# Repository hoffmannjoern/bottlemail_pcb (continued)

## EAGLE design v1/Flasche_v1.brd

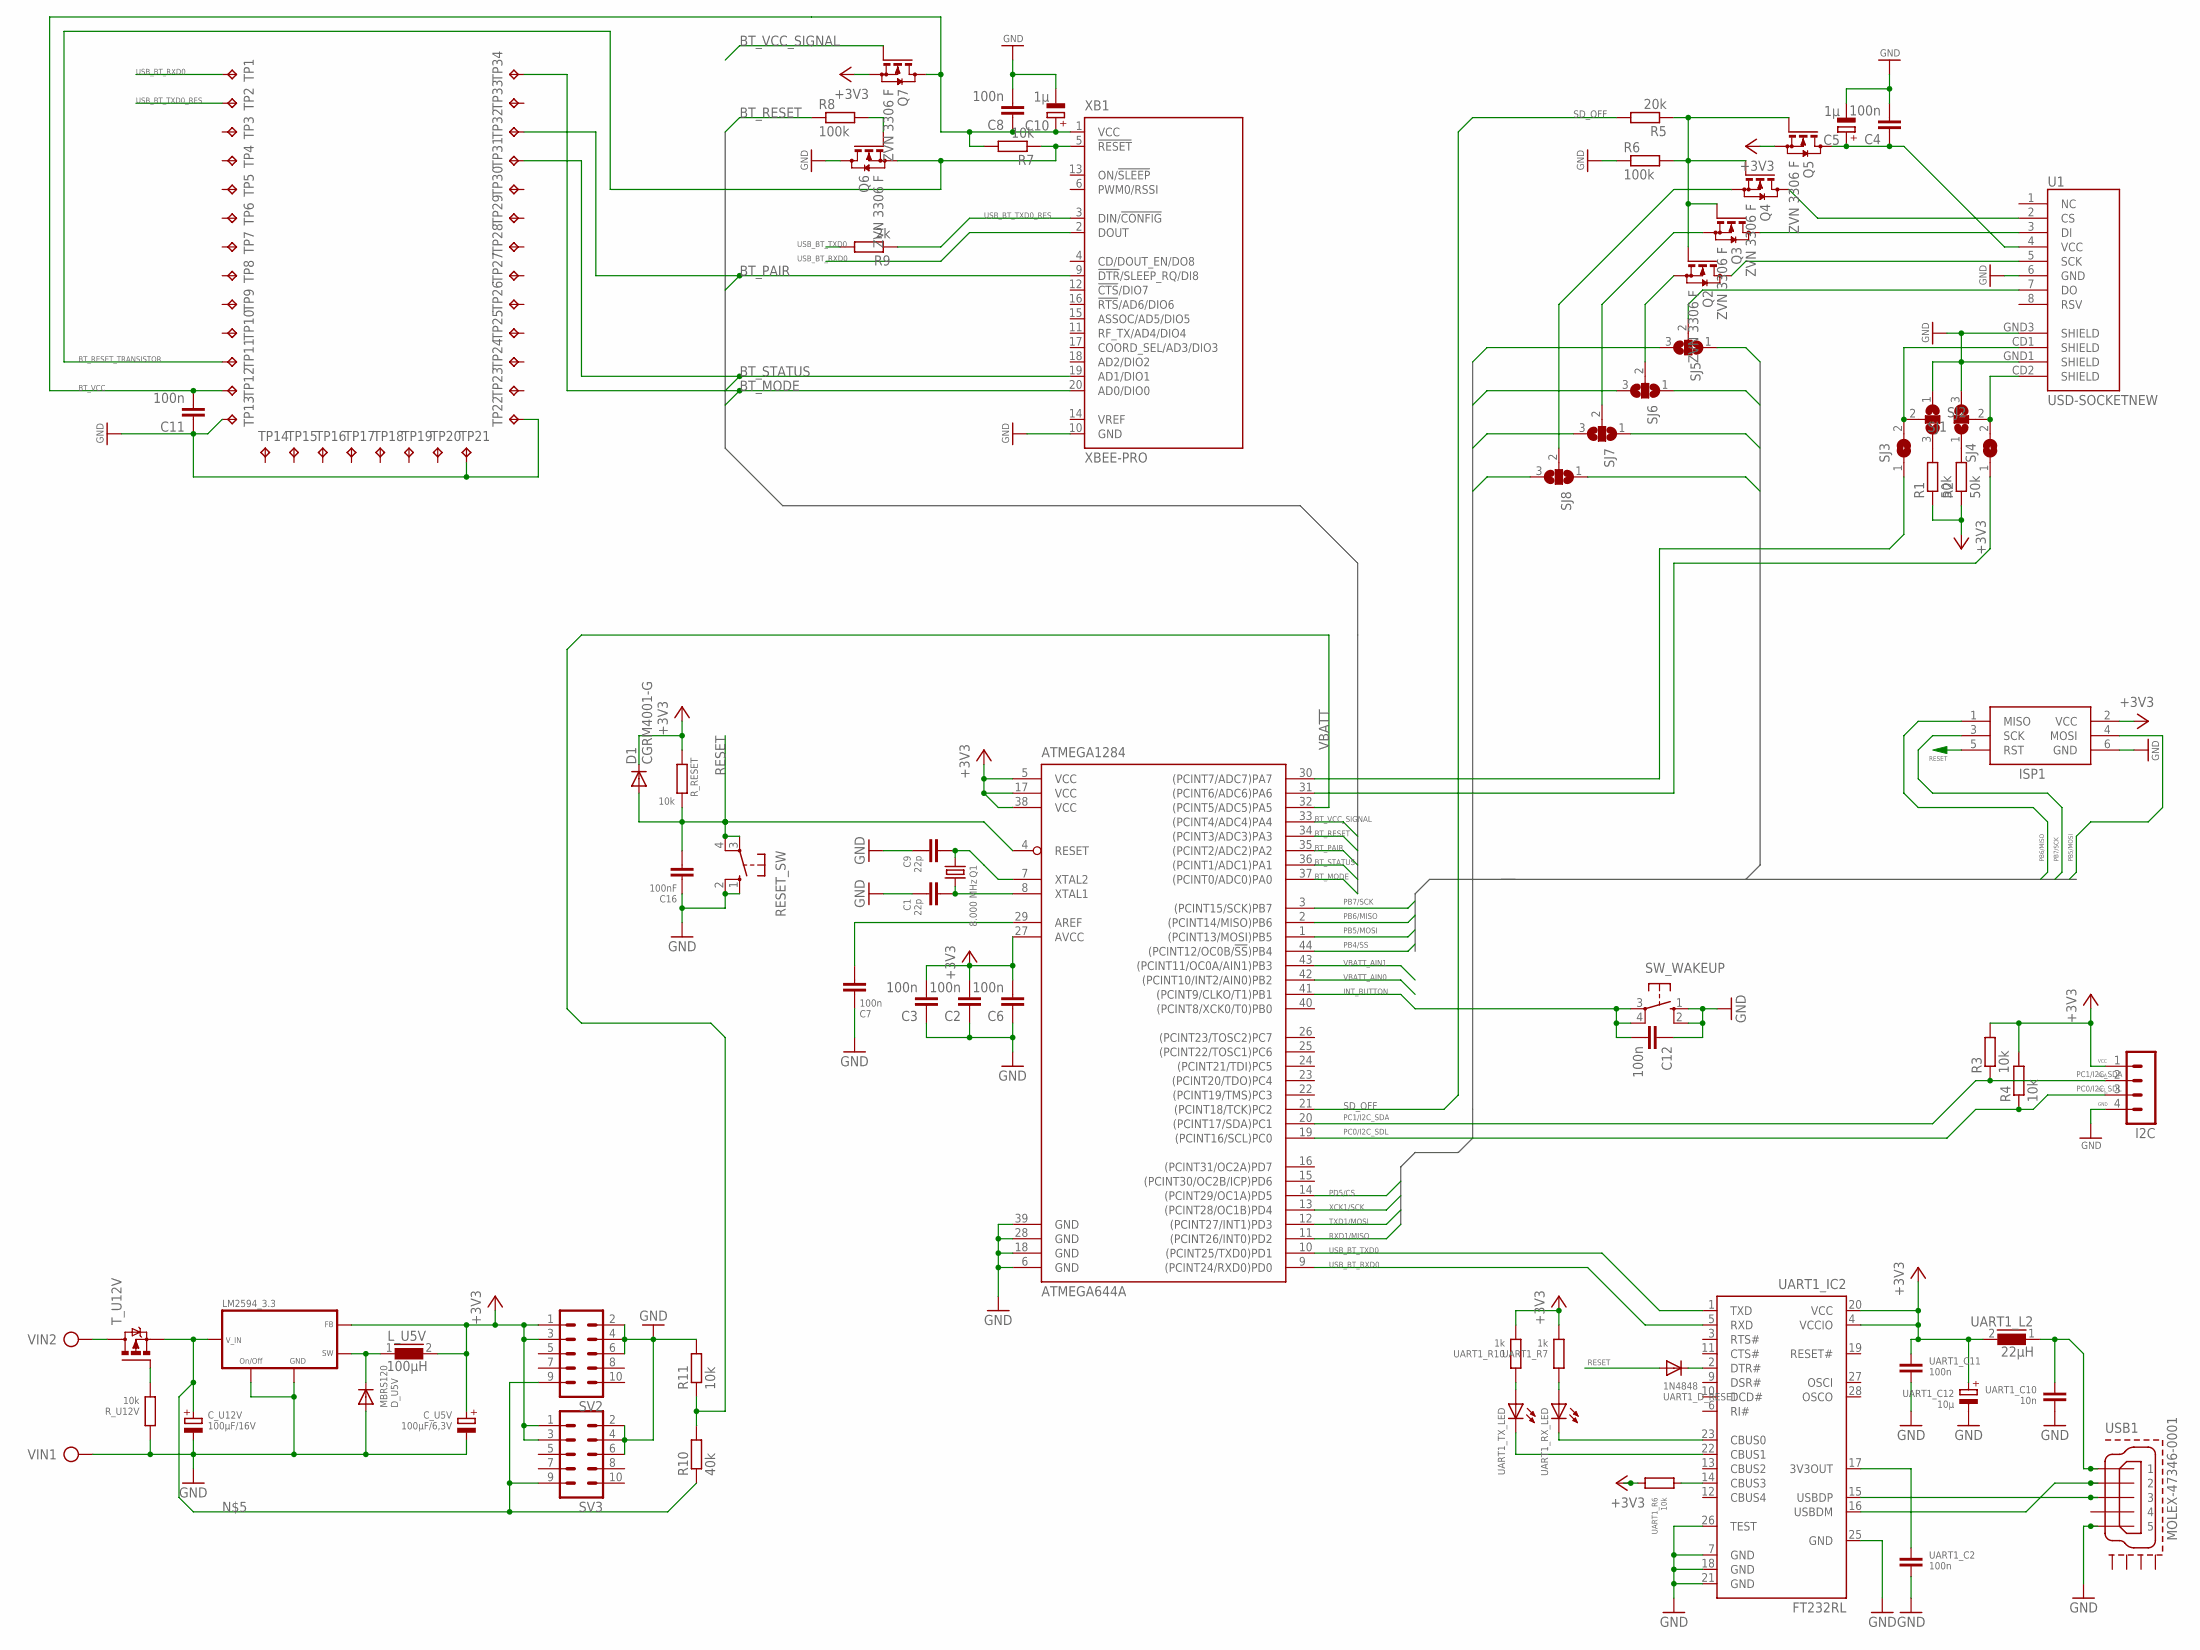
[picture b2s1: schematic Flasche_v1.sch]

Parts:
ATMEGA1284: ATMEGA644A; TQFP44
C1, C9: 22p; C0805
C2, C3, C4, C6, C7, C8, C11, C12: 100n; C0805
C5, C10: 1µ; SMC_D
C16: 100nF; C0805
C_U5V: 100µF/6,3V; SMC_D
C_U12V: 100µF/16V; SMC_D
D1: CGRM4001-G; SOD-123_MINI-SMA
D_U5V: MBRS120; SMB
I2C: MA04-1
ISP1: AVRISP-6; AVRISP
LM2594_3.3: LM2594; SO08
L_U5V: 100µH; PISM
Q1: 8.000 MHz; HC18U-V
Q2, Q3, Q4, Q5, Q6, Q7: ZVN 3306 F; SOT23
R1, R2: 50k; M1206
R3, R4, R7, R11: 10k; M1206
R5: 20k; M1206
R6, R8: 100k; M1206
R9: 2k; M1206
R10: 40k; M1206
RESET_SW: 10-XX; B3F-10XX
R_RESET: 10k; R0805
R_U12V: 10k; R0805
SJ1, SJ2, SJ5, SJ6, SJ7, SJ8: SJ2W; SJ_2
SJ3, SJ4: SJ
SV2, SV3: ML10L
SW_WAKEUP: 10-XX; B3F-10XX
TP1, TP2, TP3, TP4, TP5, TP6, TP7, TP8, TP9, TP10, TP11, TP12, TP13, TP14, TP15, TP16, TP17, TP18, TP19, TP20, TP21, TP22, TP23, TP24, TP25, TP26, TP27, TP28, TP29, TP30, TP31, TP32, TP33, TP34: TPTP06SQ; TP06SQ
T_U12V: MOS_P_SOT23_GDS; SOT23
U1: USD-SOCKETNEW; MICRO-SD-SOCKET-PP
UART1_C2, UART1_C11: 100n; C0805
UART1_C10: 10n; C0805
UART1_C12: 10µ; SMC_D
UART1_D_RESET: 1N4848; MINIMELF
UART1_IC2: FT232RL; SSOP28
UART1_L2: 22µH; PIS2408
UART1_R6: 10k; R0805
UART1_R7, UART1_R10: 1k; R0805
UART1_RX_LED, UART1_TX_LED: LEDCHIPLED_0805; CHIPLED_0805
USB1: MOLEX-47346-0001; MOLEX-47364-0001
VIN: AK350/2
XB1: XBEE-PRO

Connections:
+3V3: ATMEGA1284.5 (VCC), ATMEGA1284.17 (VCC), ATMEGA1284.27 (AVCC), ATMEGA1284.38 (VCC), C2.2, C3.2, C6.2, C_U5V.+, D1.C, I2C.1, ISP1.2 (VCC), LM2594_3.3.4 (FB), L_U5V.2, Q5.2 (S), Q7.2 (S), R1.1, R2.1, R3.2, R4.2, R_RESET.2, SV2.1, SV2.3, SV3.1, SV3.3, UART1_C11.1, UART1_C12.+, UART1_IC2.4 (VCCIO), UART1_IC2.20 (VCC), UART1_L2.2, UART1_R6.2, UART1_R7.1, UART1_R10.1
AREF: ATMEGA1284.29 (AREF), C7.2
BT_MODE: ATMEGA1284.37 ((PCINT0/ADC0)PA0), TP34.TP, XB1.20 (AD0/DIO0)
BT_PAIR: ATMEGA1284.35 ((PCINT2/ADC2)PA2), TP32.TP, XB1.9 (!DTR!/SLEEP_RQ/DI8)
BT_RESET: ATMEGA1284.34 ((PCINT3/ADC3)PA3), R8.1
BT_RESET_TRANSISTOR: Q6.2 (S), R7.1, TP11.TP, XB1.5 (!RESET)
BT_STATUS: ATMEGA1284.36 ((PCINT1/ADC1)PA1), TP31.TP, XB1.19 (AD1/DIO1)
BT_VCC: C8.1, C10.+, C11.2, Q7.3 (D), R7.2, TP12.TP, XB1.1 (VCC)
BT_VCC_SIGNAL: ATMEGA1284.33 ((PCINT4/ADC4)PA4), Q7.1 (G)
DTR#: UART1_D_RESET.C, UART1_IC2.2 (DTR#)
GND: ATMEGA1284.6 (GND), ATMEGA1284.18 (GND), ATMEGA1284.28 (GND), ATMEGA1284.39 (GND), C1.1, C2.1, C3.1, C4.2, C5.-, C6.1, C7.1, C8.2, C9.1, C10.-, C11.1, C12.1, C16.1, C_U5V.-, C_U12V.-, D_U5V.A, I2C.4, ISP1.6 (GND), LM2594_3.3.5 (ON/OFF), LM2594_3.3.6 (GND), Q6.3 (D), R6.1, R11.2, RESET_SW.1 (S), RESET_SW.2 (S1), R_U12V.2, SJ1.3, SJ2.1, SV2.2, SV2.4, SV2.6, SV3.2, SV3.4, SV3.6, SW_WAKEUP.1 (S), SW_WAKEUP.2 (S1), TP13.TP, TP21.TP, TP22.TP, U1.6 (GND), U1.GND1 (SHIELD), U1.GND3 (SHIELD), UART1_C2.2, UART1_C10.2, UART1_C11.2, UART1_C12.-, UART1_IC2.7 (GND), UART1_IC2.18 (GND), UART1_IC2.21 (GND), UART1_IC2.25 (GND), UART1_IC2.26 (TEST), USB1.5, VIN.P$1, XB1.10 (GND)
INT_BUTTON: ATMEGA1284.41 ((PCINT9/CLKO/T1)PB1), C12.2, SW_WAKEUP.3, SW_WAKEUP.4 (P1)
unnamed: UART1_R10.2, UART1_TX_LED.A
unnamed: UART1_C2.1, UART1_IC2.17 (3V3OUT)
unnamed: T_U12V.2 (D), VIN.P$2
unnamed: UART1_IC2.16 (USBDM), USB1.2
unnamed: C_U12V.+, LM2594_3.3.7 (IN), R10.1, SV2.9, SV3.9, T_U12V.3 (S)
unnamed: UART1_R7.2, UART1_RX_LED.A
unnamed: UART1_IC2.15 (USBDP), USB1.3
unnamed: UART1_IC2.14 (CBUS3), UART1_R6.1
unnamed: UART1_C10.1, UART1_L2.1, USB1.1
unnamed: UART1_IC2.23 (CBUS0), UART1_RX_LED.C
unnamed: UART1_IC2.22 (CBUS1), UART1_TX_LED.C
unnamed: SJ2.2, SJ3.2, U1.CD1 (SHIELD)
unnamed: SJ1.2, SJ4.2, U1.CD2 (SHIELD)
unnamed: R_U12V.1, T_U12V.1 (G)
unnamed: ATMEGA1284.31 ((PCINT6/ADC6)PA6), SJ4.1
unnamed: R1.2, SJ2.3
unnamed: R2.2, SJ1.1
unnamed: SJ5.2, U1.7 (DO)
unnamed: ATMEGA1284.30 ((PCINT7/ADC7)PA7), SJ3.1
unnamed: Q2.2 (S), SJ6.2
unnamed: Q3.2 (S), SJ7.2
unnamed: Q4.3 (D), U1.2 (CS)
unnamed: Q3.3 (D), U1.3 (DI)
unnamed: Q2.3 (D), U1.5 (SCK)
unnamed: C4.1, C5.+, Q5.3 (D), U1.4 (VCC)
unnamed: Q2.1 (G), Q3.1 (G), Q4.1 (G), Q5.1 (G), R5.1, R6.2
unnamed: Q6.1 (G), R8.2
PB4/SS: ATMEGA1284.44 ((PCINT12/OC0B/!SS!)PB4), SJ8.1
PB5/MOSI: ATMEGA1284.1 ((PCINT13/MOSI)PB5), ISP1.4 (MOSI), SJ7.1
PB6/MISO: ATMEGA1284.2 ((PCINT14/MISO)PB6), ISP1.1 (MISO), SJ5.1
PB7/SCK: ATMEGA1284.3 ((PCINT15/SCK)PB7), ISP1.3 (SCK), SJ6.1
PC0/I2C_SDL: ATMEGA1284.19 ((PCINT16/SCL)PC0), I2C.3, R4.1
PC1/I2C_SDA: ATMEGA1284.20 ((PCINT17/SDA)PC1), I2C.2, R3.1
PD5/CS: ATMEGA1284.14 ((PCINT29/OC1A)PD5), SJ8.3
RESET: ATMEGA1284.4 (RESET), C16.2, D1.A, ISP1.5 (RST), RESET_SW.3, RESET_SW.4 (P1), R_RESET.1, UART1_D_RESET.A
RXD1/MISO: ATMEGA1284.11 ((PCINT26/INT0)PD2), SJ5.3
SD_CS: Q4.2 (S), SJ8.2
SD_OFF: ATMEGA1284.21 ((PCINT18/TCK)PC2), R5.2
SWITCH_OUT: D_U5V.C, LM2594_3.3.8 (SW), L_U5V.1
TXD1/MOSI: ATMEGA1284.12 ((PCINT27/INT1)PD3), SJ7.3
USB_BT_RXD0: ATMEGA1284.9 ((PCINT24/RXD0)PD0), TP1.TP, UART1_IC2.5 (RXD), XB1.2 (DOUT)
USB_BT_TXD0: ATMEGA1284.10 ((PCINT25/TXD0)PD1), R9.2, UART1_IC2.1 (TXD)
USB_BT_TXD0_RES: R9.1, TP2.TP, XB1.3 (DIN/!CONFIG)
VBATT: ATMEGA1284.32 ((PCINT5/ADC5)PA5), R10.2, R11.1
VBATT_AIN0: ATMEGA1284.42 ((PCINT10/INT2/AIN0)PB2)
VBATT_AIN1: ATMEGA1284.43 ((PCINT11/OC0A/AIN1)PB3)
XCK1/SCK: ATMEGA1284.13 ((PCINT28/OC1B)PD4), SJ6.3
XTAL1: ATMEGA1284.8 (XTAL1), C1.2, Q1.1
XTAL2: ATMEGA1284.7 (XTAL2), C9.2, Q1.2

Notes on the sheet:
VCC
SDA
SCL
GND

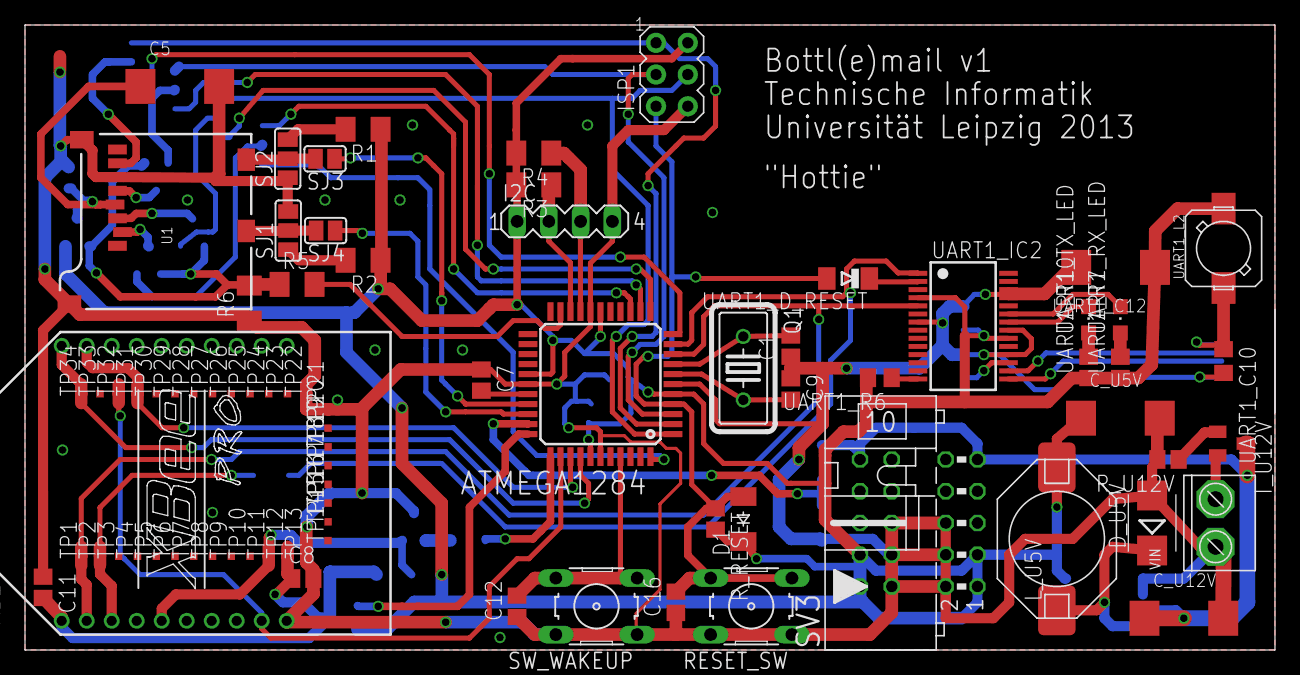
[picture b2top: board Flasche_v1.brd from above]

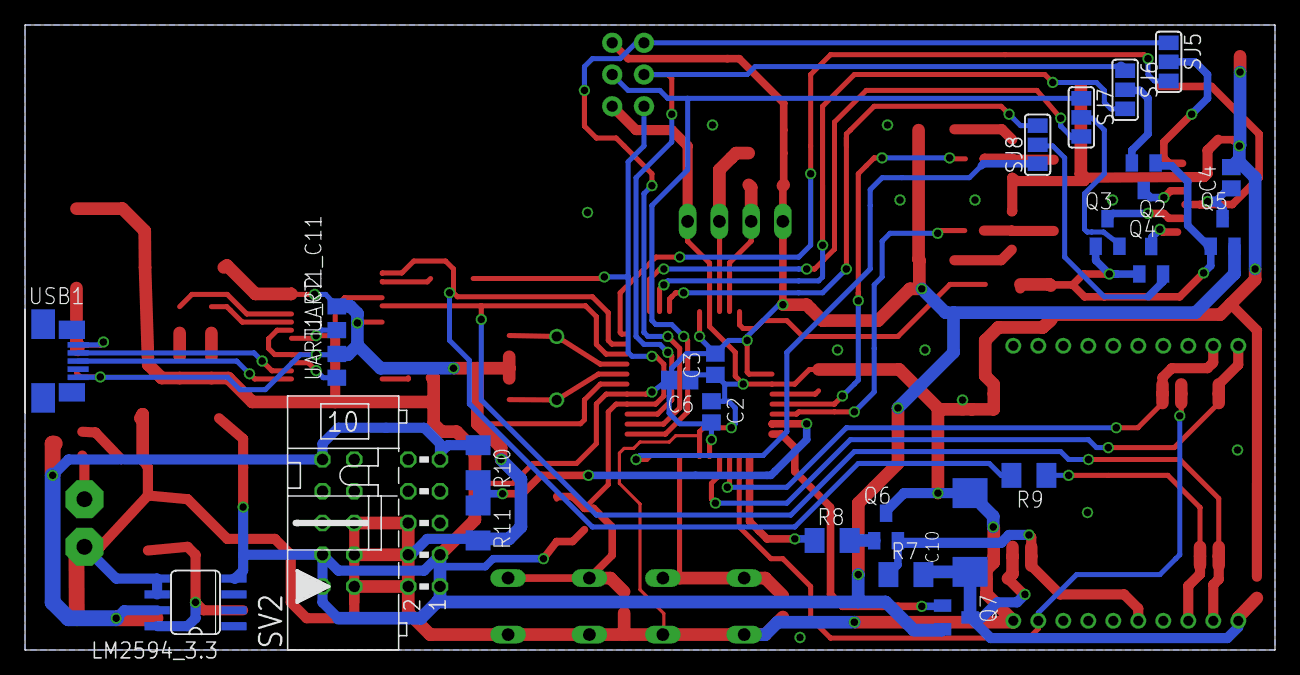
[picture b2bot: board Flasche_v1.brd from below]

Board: 2 copper layers, 100.0 x 50.0 mm, 105 parts (25 on the bottom side), 59 nets.

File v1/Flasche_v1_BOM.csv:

Qty;Value;Device;Package;Parts;Description;MF;MPN;OC_FARNELL;OC_NEWARK;TP_SIGNAL_NAME
2;;10-XX;B3F-10XX;RESET_SW, SW_WAKEUP;OMRON SWITCH;;B3F-1000;176432;36M3542;
2;;LEDCHIPLED_0805;CHIPLED_0805;UART1_RX_LED, UART1_TX_LED;LED;;;;;
1;;MA04-1;MA04-1;I2C;PIN HEADER;;;unknown;unknown;
2;;ML10L;ML10L;SV2, SV3;HARTING;;;unknown;unknown;
1;;MOS_P_SOT23_GDS;SOT23;T_U12V;P - CHANNEL ENHANCEMENT MODE (POWER ) MOS TRANSISTOR;;;;;
2;;SJ;SJ;SJ3, SJ4;SMD solder JUMPER;;;;;
6;;SJ2W;SJ_2;SJ1, SJ2, SJ5, SJ6, SJ7, SJ8;SMD solder JUMPER;;;;;
2;100k;R-EU_M1206;M1206;R6, R8;RESISTOR, European symbol;;;;;
8;100n;C-0805;C0805;C2, C3, C4, C6, C7, C8, C11, C12;Capacitor;;;;;
2;100n;C-EUC0805;C0805;UART1_C2, UART1_C11;CAPACITOR, European symbol;;;;;
1;100nF;C-0805;C0805;C16;Capacitor;;;;;
1;100µF/16V;CPOL-EUSMCD;SMC_D;C_U12V;POLARIZED CAPACITOR, European symbol;;;;;
1;100µF/6,3V;CPOL-EUSMCD;SMC_D;C_U5V;POLARIZED CAPACITOR, European symbol;;;;;
1;100µH;L_PISM;PISM;L_U5V;INDUCTOR;;;;;
4;10k;R-EU_M1206;M1206;R3, R4, R7, R11;RESISTOR, European symbol;;;;;
1;10k;R-EU_R0805;R0805;UART1_R6;RESISTOR, European symbol;;;;;
2;10k;R-R0805;R0805;R_RESET, R_U12V;Resistor;;;;;
1;10n;C-EUC0805;C0805;UART1_C10;CAPACITOR, European symbol;;;;;
1;10µ;CPOL-EUSMCD;SMC_D;UART1_C12;POLARIZED CAPACITOR, European symbol;;;;;
1;1N4848;D_MINIMELF;MINIMELF;UART1_D_RESET;DIODE;;;;;
2;1k;R-R0805;R0805;UART1_R7, UART1_R10;Resistor;;;;;
2;1µ;CPOL-EUSMCD;SMC_D;C5, C10;POLARIZED CAPACITOR, European symbol;;;;;
1;20k;R-EU_M1206;M1206;R5;RESISTOR, European symbol;;;;;
2;22p;C-0805;C0805;C1, C9;Capacitor;;;;;
1;22µH;L_PIS2408;PIS2408;UART1_L2;INDUCTOR;;;;;
1;2k;R-EU_M1206;M1206;R9;RESISTOR, European symbol;;;;;
1;40k;R-EU_M1206;M1206;R10;RESISTOR, European symbol;;;;;
2;50k;R-EU_M1206;M1206;R1, R2;RESISTOR, European symbol;;;;;
1;8.000 MHz;CRYSTALHC18U-V;HC18U-V;Q1;CRYSTAL;;;unknown;unknown;
1;AK350/2;AK350/2;AK350/2;VIN;CONNECTOR Raster: 3,5mm;;;;;
1;ATMEGA644A;ATMEGA644A;TQFP44;ATMEGA1284;8-bit Microcontroller with 64K Bytes In-System Programmable Flash;;ATMEGA644PV-10AU;1455123;58M3748;
1;AVRISP-6;AVRISP-6;AVRISP;ISP1;AVR ISP HEADER;;;;;
1;CGRM4001-G;CGRM4001-G;SOD-123_MINI-SMA;D1;Molded plasitc,JEDEC SOD-123/Mini SMA;;;;;
1;FT232RL;FT232RL;SSOP28;UART1_IC2;Source: http://www.ftdichip.com/Documents/DataSheets/DS_FT232R_v104.pdf;;;;;
1;LM2594;LM2594;SO08;LM2594_3.3;LM2594/LM2594HV;;;;;
1;MBRS120;D_SMB;SMB;D_U5V;DIODE;;;;;
1;MOLEX-47346-0001;MOLEX-47346-0001;MOLEX-47364-0001;USB1;MICRO USB B, BOTTOM MOUNT;;;;;
34;TPTP06SQ;TPTP06SQ;TP06SQ;TP1, TP2, TP3, TP4, TP5, TP6, TP7, TP8, TP9, TP10, TP11, TP12, TP13, TP14, TP15, TP16, TP17, TP18, TP19, TP20, TP21, TP22, TP23, TP24, TP25, TP26, TP27, TP28, TP29, TP30, TP31, TP32, TP33, TP34;Test pad;;;;;
1;USD-SOCKETNEW;USD-SOCKETNEW;MICRO-SD-SOCKET-PP;U1;microSD Socket;;;;;
1;XBEE-PRO;XBEE-PRO;XBEE-PRO;XB1;XBee (TM) /XBee-PRO(TM) OEM RF Modules;;XBP24-AWI-001;1337916;42M2667;
6;ZVN 3306 F;BSS123;SOT23;Q2, Q3, Q4, Q5, Q6, Q7;N-CHANNEL MOS FET;;;;;

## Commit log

2014-08-04 - add images of v1
2014-08-04 - add schematic
2014-08-04 - remove unneeded pdfs
2014-08-04 : add versions from git
2014-09-10 Initial commit, latest PCB version from end of project in 2013
2014-09-10 - Added Arduino Shield headers - cleaned up the schmeatic and grouped modules on sheets by function - inserted and de-crossed bus systems - started to unify font sizes and pin / netwrok naming
2014-09-28 - employes Seeduino Open Parts Library for groove connectors and possibly more in the future - added groove connectors
2014-09-28 - changed old BTBee Pro specific socketing into more generic XBEE socket
2014-09-28 - added FTDI serial connector - employed sparkfun lib for connectors
2014-09-28 - connected FTDI and XBEE Socket
2014-09-28 - added some more frames for structure
2014-09-28 - overhauled and simplified SD card connection - decided to stick with the sparkfun socket, as it's cheap and available by now
2014-09-29 - added HM11 BT Module - employed component device exported from SeedStudio BLE_Bee_v1.0 schematic
2014-09-29 - employed several more libraries from Seed Studio and Arduino Project - replaced power supply with modern solution, charging circuitry etc.
2014-09-29 - replaces mini USB B connector with SparkFun version
2014-09-29 - cleaned up and unified many discrete components - set Reichelt Order Numbers for all capacitors
2014-10-01 - unified, replaced and checked all components - added vendor IDs and order information to all components - generated BOMs
2014-10-01 - merged BOMs - BOM_Merged.csv is checked for correctness and completeness - minor adjustments in Device Values for unification
2014-10-03 - replaced Diodes with lower quality version, as they are easier to get - added important BOM information
